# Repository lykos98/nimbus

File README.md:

# Nimbus project
Self build weather sensor network, experimenting on esp32, WiFi, LoRa and much more. 

## Aim of the project 
Hi! I am a PhD student in Data Science and I love to build stuff with microcontrollers and similar things. 
Here I will document my journey in building my weather sensors network, something like [https://sensor.community] but with more flexibility.

The idea is to open source all the kits, parts and codes, and also the instructions to build weather stations. 
Maybe one day to share these kits among people, and to grow a community around citizen science. 

## Project Structure
This repository is organized into several components:

- **[Data API (Backend)](backend/data_api/README.md)**: Flask-based REST API for data ingestion and retrieval.
- **Frontend**: Dashboard and admin interface (documentation pending).
- **PCB**: KiCad designs for the weather station boards.
- **Station Scripts**: Firmware for ESP32 and other microcontrollers.

## TODO
Frontend:
- fix thing date in axis of plots
- improve overall look
- expand admin panel with profiles
    - each one profile is associated to stations, can see secrets can modify description of stations.
    - admin can see anything
    - user can see its station
    - user can set visibility of the station in the pubblic dashboard
    - admin can see all stations with messages and users 
- misc:
    - each station has a message queue that can be seen from the admin, in particular, you should be able to see the message queue for each station in order to get info on a status, like healthy and so on

Backend

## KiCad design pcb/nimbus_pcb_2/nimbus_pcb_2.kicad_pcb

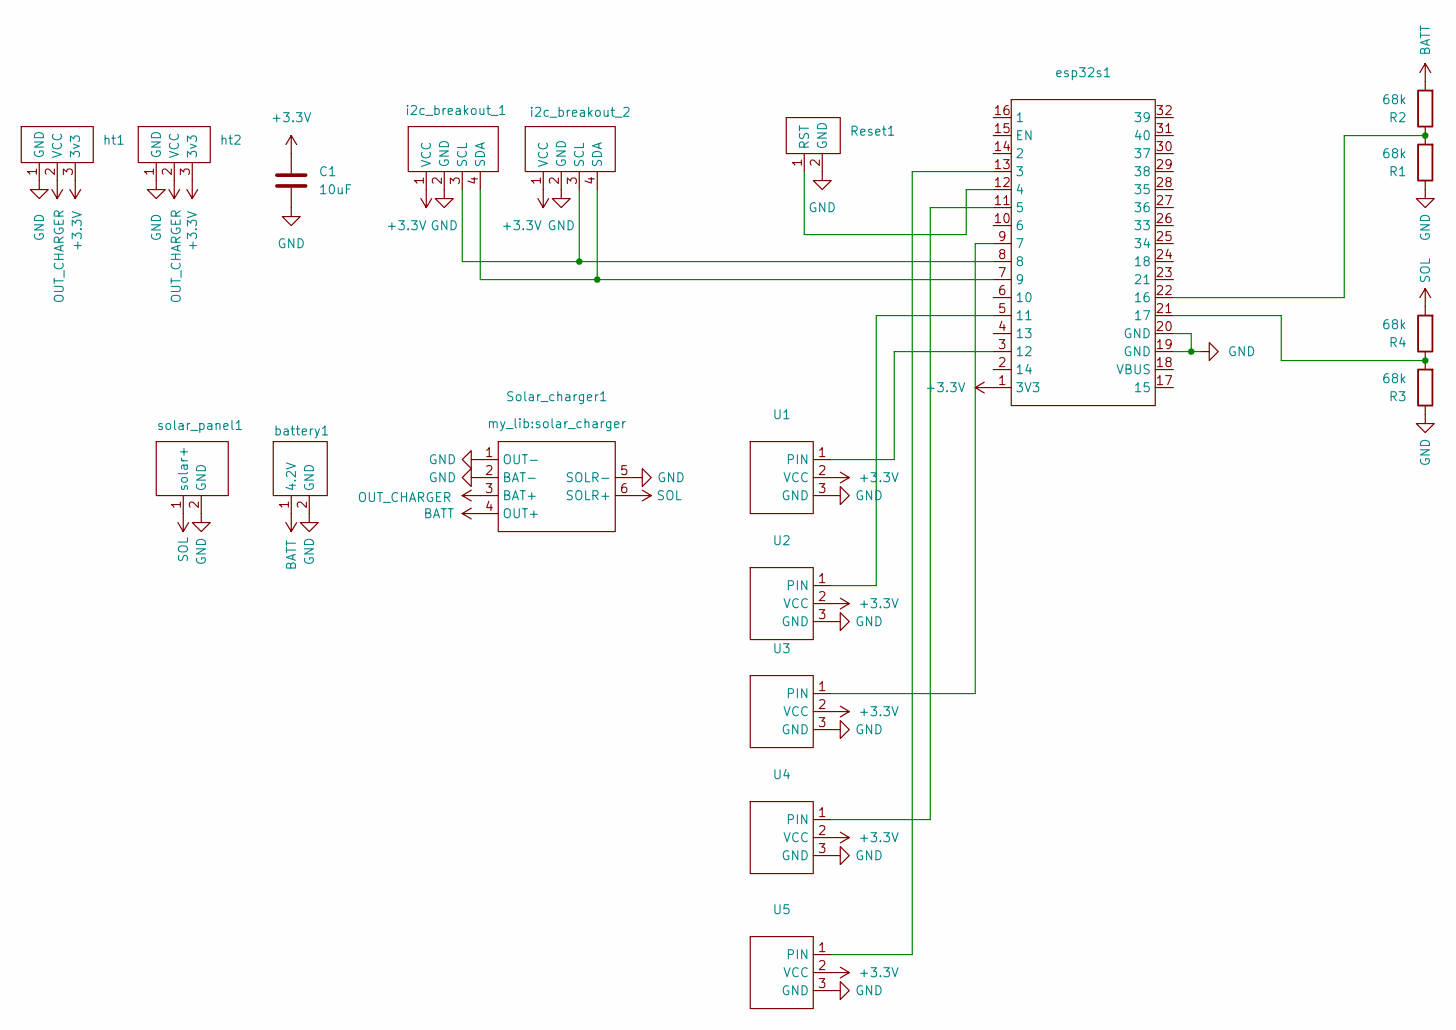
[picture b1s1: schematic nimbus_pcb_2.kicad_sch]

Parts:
C1: 10uF; C_Disc_D9.0mm_W2.5mm_P5.00mm
R1, R2, R3, R4: 68k; R_Axial_DIN0309_L9.0mm_D3.2mm_P15.24mm_Horizontal
Reset1: reset
Solar_charger1: solar_charger
U1, U2, U3, U4, U5: pin_breakout
battery1: battery
esp32s1: esp32s2
ht1, ht2: ht7833
i2c_breakout_1, i2c_breakout_2: i2c_breakout
solar_panel1: solar

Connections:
+3.3V: C1.1, U1.2 (VCC), U2.2 (VCC), U3.2 (VCC), U4.2 (VCC), U5.2 (VCC), esp32s1.1 (3V3), ht1.3 (3v3), ht2.3 (3v3), i2c_breakout_1.1 (VCC), i2c_breakout_2.1 (VCC); also elsewhere on the board
BATT: R2.2, Solar_charger1.4 (OUT+), battery1.1 (4.2V)
GND: C1.2, R1.1, R3.1, Reset1.2 (GND), Solar_charger1.1 (OUT-), Solar_charger1.2 (BAT-), Solar_charger1.5 (SOLR-), U1.3 (GND), U2.3 (GND), U3.3 (GND), U4.3 (GND), U5.3 (GND), battery1.2 (GND), esp32s1.19 (GND), esp32s1.20 (GND), ht1.1 (GND), ht2.1 (GND), i2c_breakout_1.2 (GND), i2c_breakout_2.2 (GND), solar_panel1.2 (GND); also elsewhere on the board
unnamed 3: Reset1.1 (RST), esp32s1.12 (4); also elsewhere on the board
unnamed 4: U1.1 (PIN), esp32s1.3 (12); also elsewhere on the board
unnamed 5: U2.1 (PIN), esp32s1.5 (11); also elsewhere on the board
unnamed 6: U3.1 (PIN), esp32s1.9 (7); also elsewhere on the board
unnamed 7: U4.1 (PIN), esp32s1.11 (5); also elsewhere on the board
unnamed 8: U5.1 (PIN), esp32s1.13 (3); also elsewhere on the board
unnamed 9: esp32s1.7 (9), i2c_breakout_1.4 (SDA), i2c_breakout_2.4 (SDA); also elsewhere on the board
unnamed 10: R1.2, R2.1, esp32s1.22 (16); also elsewhere on the board
unnamed 11: R3.2, R4.1, esp32s1.21 (17); also elsewhere on the board
unnamed 12: esp32s1.8, i2c_breakout_1.3 (SCL), i2c_breakout_2.3 (SCL); also elsewhere on the board
OUT_CHARGER: Solar_charger1.3 (BAT+), ht1.2 (VCC), ht2.2 (VCC)
SOL: R4.2, Solar_charger1.6 (SOLR+), solar_panel1.1 (solar+)

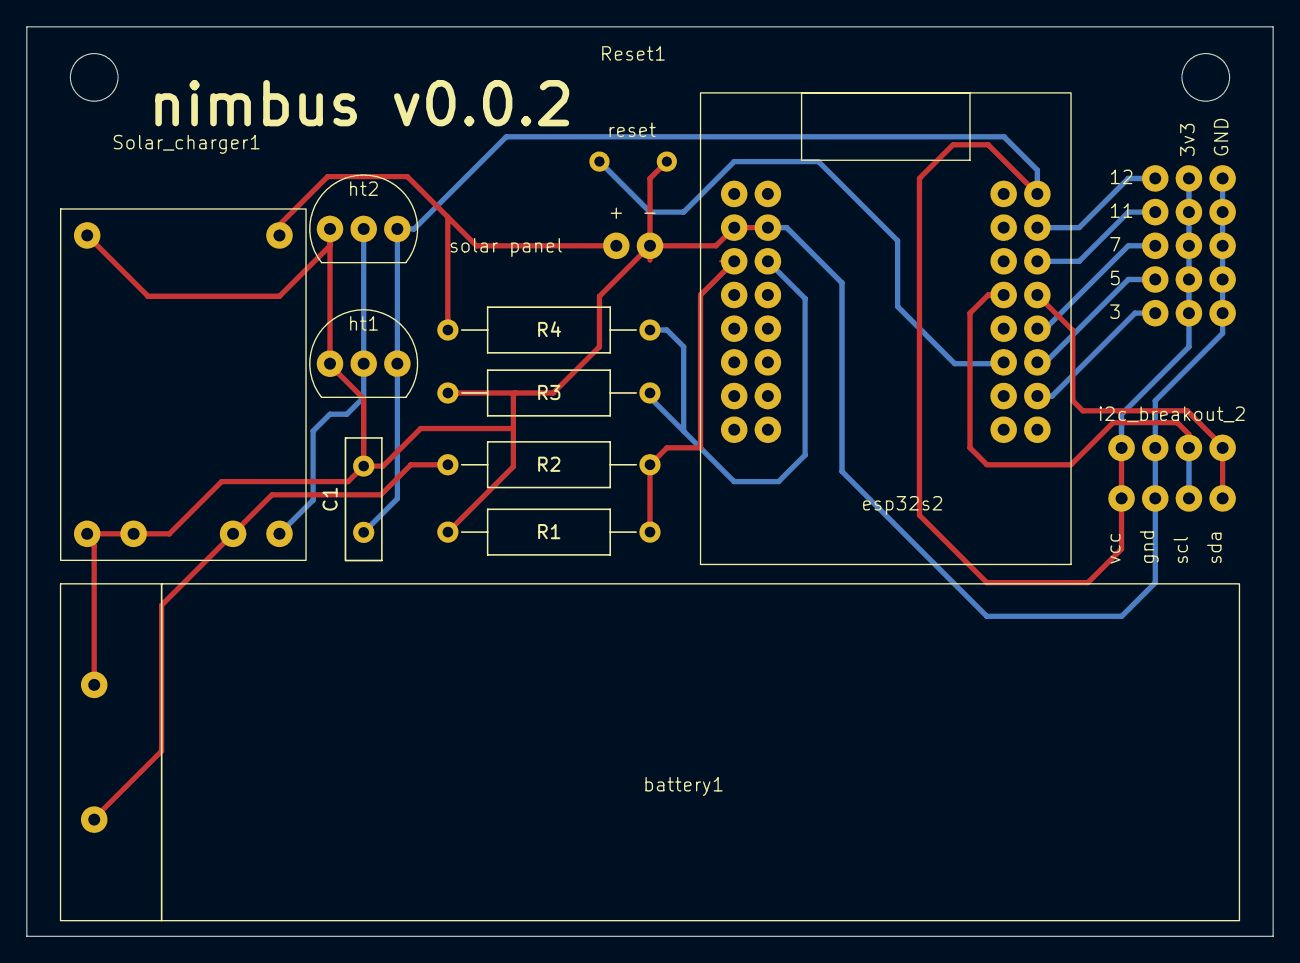
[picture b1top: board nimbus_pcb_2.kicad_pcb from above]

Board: 2 copper layers, 94.0 x 68.6 mm, 19 parts (0 on the bottom side), 15 nets.

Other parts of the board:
esp32s2: esp32s2

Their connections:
+3.3V: esp32s2.1 (3V3); also elsewhere on the board
GND: esp32s2.19 (GND), esp32s2.20 (GND); also elsewhere on the board
unnamed 3: esp32s2.12 (4); also elsewhere on the board
unnamed 4: esp32s2.3 (12); also elsewhere on the board
unnamed 5: esp32s2.5 (11); also elsewhere on the board
unnamed 6: esp32s2.9 (7); also elsewhere on the board
unnamed 7: esp32s2.11 (5); also elsewhere on the board
unnamed 8: esp32s2.13 (3); also elsewhere on the board
unnamed 9: esp32s2.7 (9); also elsewhere on the board
unnamed 10: esp32s2.22 (16); also elsewhere on the board
unnamed 11: esp32s2.21 (17); also elsewhere on the board
unnamed 12: esp32s2.8; also elsewhere on the board

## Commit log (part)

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2023-10-03 added mqttLogger
2023-10-03 fixed bugs
2023-10-03 fixed path
2023-10-07 added user mosquitto
2024-03-17 added catch
2024-03-19 added bugfix
2024-04-06 added blacklist
2024-10-05 added dash frontend
2024-10-05 added dockerfile
2024-10-10 added window selection in dash
2024-10-13 added mobile support hopefully
2024-10-13 fixed mobile
2024-10-16 added date fix
2024-10-18 added compose
2024-10-18 expreimenting with compose
2024-11-01 added file server for ca
2024-11-02 corrected loader
2024-11-03 added configurator for name of the station
2024-12-08 added wind speed
2024-12-08 added windspeed graph
2025-03-14 added visualization for wind direction
2025-03-16 added pretty plot
2025-03-17 corrected bug on unwanted nans
2025-03-17 eliminated prints
2025-03-17 added the nan things
2025-03-20 refactored code and added pcbs
2025-04-13 added error handling in mqtt logger
2025-04-17 added containerized logger
2025-04-18 added hour correction
2025-04-22 added correction to dashboard
2025-05-31 added esp32_c3 station script
2025-07-19 added valid fields thing
2025-07-19 added slim python image
2025-07-20 added proto implementation of api
2025-07-25 hopefully finished migration
2025-07-26 added correction of timezone
2025-07-26 fixed bug on windows
2025-07-26 added try except
2025-09-08 fixed thing
2025-10-16 added script for station
2025-11-29 feat: Implement InfluxDB and User/Station Management System
    Integrates InfluxDB, adds user/station management, and introduces a new admin dashboard. Updates data_api for JWT auth and database connectivity. Orchestrates all services with a root docker-compose.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
2025-11-30 added env variables
2025-11-30 added error log
2025-11-30 corrected vibecoding errors
2025-11-30 maybe corrected jsonification and data api
2025-11-30 fixed user issue with postgres
2025-11-30 fixed user with dashboard
2025-11-30 fixed user with admin
2025-11-30 trying new dashboard thing
2025-11-30 boh trying
2025-11-30 added fix
2025-11-30 copy
2026-01-29 saved symbols
2026-02-24 added station scripts
2026-02-27 added readme
2026-02-27 updated main readme
2026-03-11 fixed gui glitch on dash
2026-03-18 frontend-additions
2026-03-20 added migration sql table
2026-03-20 added logging on data api
2026-03-20 vibe coded frontend for admin panel
2026-03-20 updated also backend
2026-03-24 updated ulimits for influx
2026-03-28 added error fallback and write to logs
2026-04-08 added create station button
2026-04-13 fixed gui on admin panel
2026-04-15 added terrain
2026-04-16 added svg for terrain hum
2026-04-19 updated compose
2026-04-26 added failover to flask request
